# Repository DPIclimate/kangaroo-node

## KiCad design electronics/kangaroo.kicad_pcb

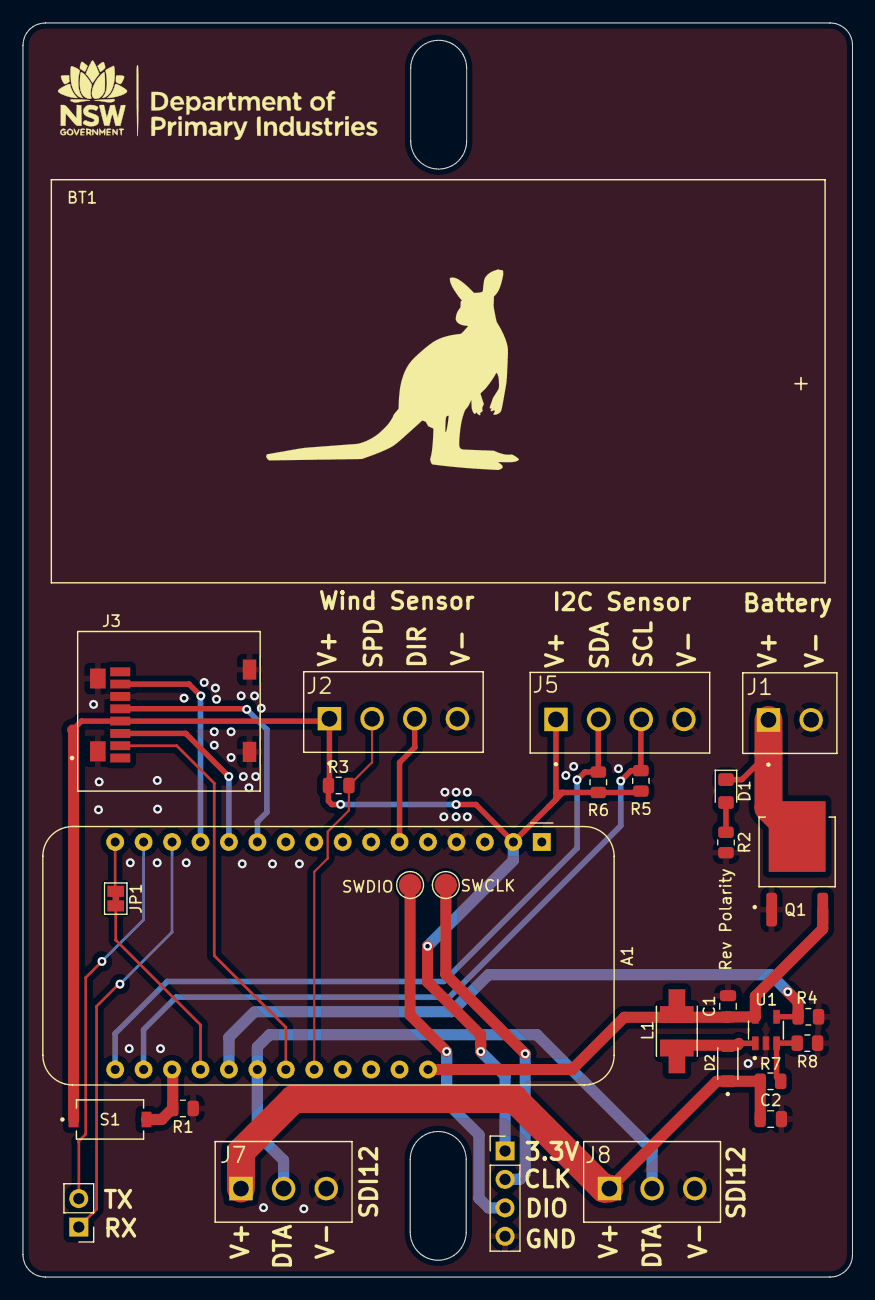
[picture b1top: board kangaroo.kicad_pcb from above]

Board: 2 copper layers, 74.1 x 112.0 mm, 29 parts (0 on the bottom side), 25 nets.

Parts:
A1: Adafruit_Feather_M0_RFM9x_LoRa_Radio; Adafruit_Feather_M0_RFM
BT1: BHDL
C1: 2.2uF; C_0805_2012Metric
C2: 10uF; C_0805_2012Metric
D1: LED; LED_0805_2012Metric_Pad1.15x1.40mm_HandSolder
D2: SS34LW_RVG; SODFL3718X102N
J1: TBP02R2-381-02BE; CUI_TBP02R2-381-02BE
J2, J5: TBP02R2-381-04BE; CUI_TBP02R2-381-04BE
J3: ST1W008S4AR1500; JAE_ST1W008S4AR1500
J4: Conn_01x02_Female; PinHeader_1x02_P2.54mm_Vertical
J6: Conn_01x04_Female; PinHeader_1x04_P2.54mm_Vertical
J7, J8: TBP02R2-381-03BE; CUI_TBP02R2-381-03BE
JP1: Jumper_2_Bridged; SolderJumper-2_P1.3mm_Bridged_Pad1.0x1.5mm
L1: LQH43CN100K03L; IND_LQH43CN100K03L
Q1: AOD417; DPAK228P994X240_3N
R1: 10K; R_0805_2012Metric
R2: 320; R_0805_2012Metric
R3, R5, R6: 4.7K; R_0805_2012Metric
R4: 100K; R_0805_2012Metric
R7: 43.3K; R_0805_2012Metric
R8: 5K; R_0805_2012Metric
S1: PTS636_SM43J_SMTR_LFS; SW_PTS636_SM43J_SMTR_LFS
SWCLK: SWCLK; TestPoint_Pad_D2.0mm
SWDIO: SWDIO; TestPoint_Pad_D2.0mm
U1: MIC2288YD5-TR; SOT95P280X100-5N

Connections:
12V_EN: A1.21 (D9), R4.2, U1.4 (EN)
+3.3V: A1.2 (3V3), J2.1, J3.4, J5.1, J6.1, R3.2, R5.2, R6.2, S1.1
+12V: C2.1, D2.C, J7.1, J8.1, R7.2
+BATT: A1.28 (VBAT), C1.1, L1.1, Q1.3, U1.5 (VIN)
GND: A1.4 (GND), C1.2, C2.2, J1.2, J2.4, J3.6, J3.GND1 (GND), J3.GND2 (GND), J3.GND3 (GND), J3.GND4 (GND), J5.4, J6.4, J7.3, J8.3, Q1.1, R1.1, R2.2, R4.1, R8.1, U1.2 (GND)
I2C_SCL: A1.18 (SCL/D21), J5.3, R5.1
I2C_SDA: A1.17 (SDA/D20), J5.2, R6.1
LORA_CONN: A1.20 (D6), JP1.2 (B)
LORA_TEST: A1.19 (D5), R1.2, S1.2
unnamed: A1.16 (DIO1), JP1.1 (A)
unnamed: D1.1 (K), J1.1, Q1.4
unnamed: D1.2 (A), R2.1
unnamed: D2.A, L1.2, U1.1 (SW)
unnamed: J6.2, SWCLK.1
unnamed: J6.3, SWDIO.1
unnamed: R7.1, R8.2, U1.3 (FB)
RX: A1.14 (RX/D0), J4.1
SDI12_DATA: A1.22 (D10), J7.2, J8.2
SPI_CS: A1.23 (D11), J3.2
SPI_MISO: A1.13 (MISO/D22), J3.7
SPI_MOSI: A1.12 (MOSI/D23), J3.3
SPI_SCK: A1.11 (SCK/D24), J3.5
TX: A1.15 (TX/D1), J4.2
WIND_DIR: A1.6 (A1), J2.3
WIND_SPD: A1.24 (D12), J2.2, R3.1

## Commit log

2022-11-02 v1.0.0 moved from enviro-node project.
2022-11-11 Another couple of wake from standby workarounds added.
2023-12-11 Stripped to a bare read/uplink cycle. The uplink code waits for LMIC_queryTxReady to be true before sleeping on the assumption that means all MAC command processing has been done.
2023-12-13 WIP: Changed SDI-12 power enable pin (still need to fix schematic), join loop all in setup now.
2023-12-13 WIP: Event system code integration to count wind pulses while asleep.
2024-01-23 Adjustment to wind speed first-reading-flag-value and subtracted a second from the sleep time.
